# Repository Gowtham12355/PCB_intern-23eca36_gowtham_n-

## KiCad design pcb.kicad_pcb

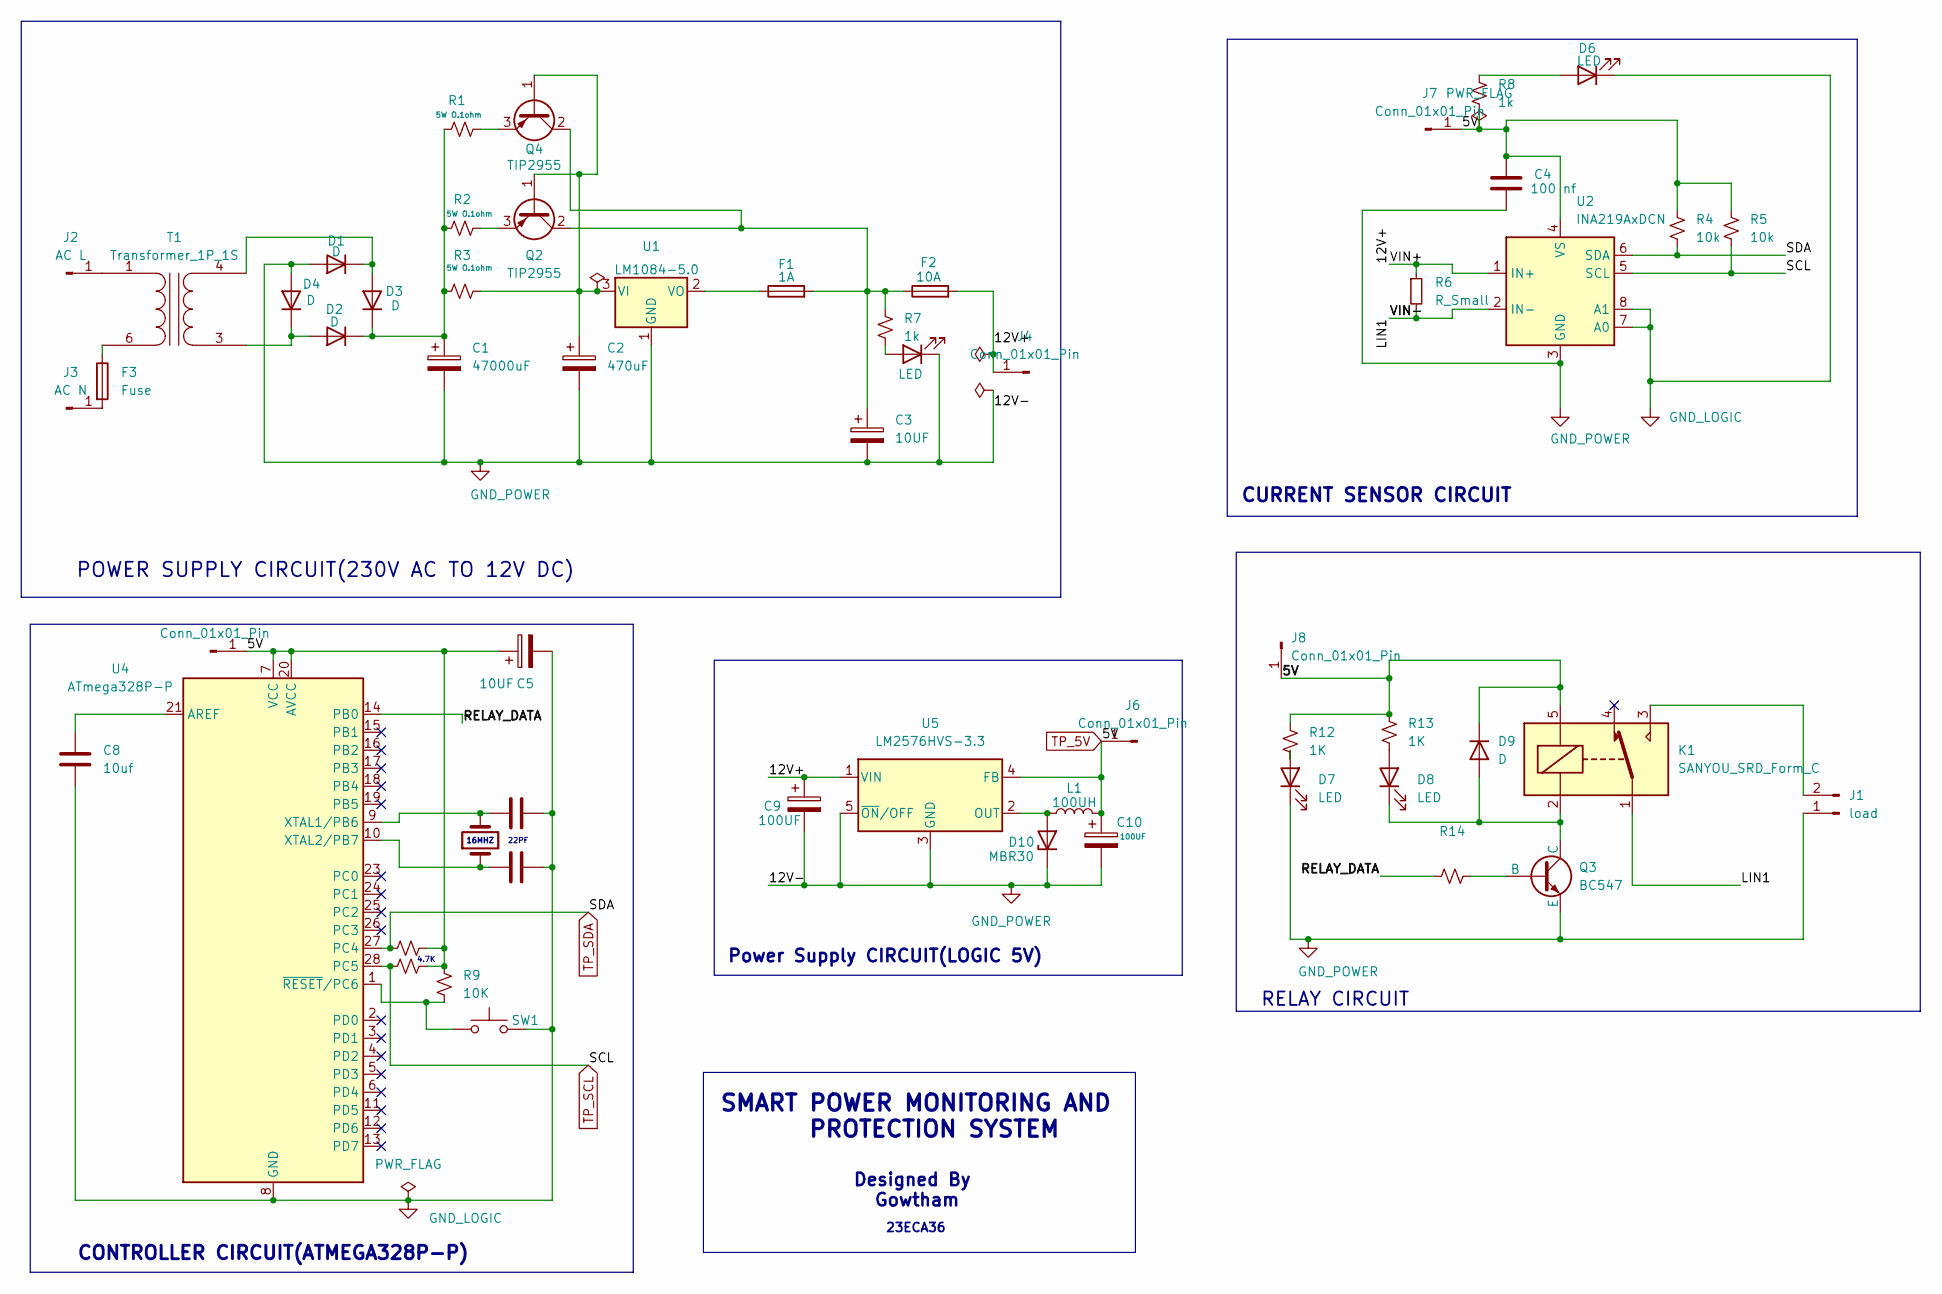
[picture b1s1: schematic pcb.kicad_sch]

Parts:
C1: 47000uF; CP_Radial_D18.0mm_P7.50mm
C2: 470uF; CP_Radial_D8.0mm_P5.00mm
C3: 10UF; CP_Radial_D8.0mm_P5.00mm
C4: 100 nf; C_0603_1608Metric
C5: 10UF; CP_Elec_6.3x5.7
C6, C7: C; C_0603_1608Metric_Pad1.08x0.95mm_HandSolder
C8: 10uf; C_0603_1608Metric_Pad1.08x0.95mm_HandSolder
C9, C10: 100UF; C_1210_3225Metric_Pad1.33x2.70mm_HandSolder
D1, D2, D3, D4: D; D_DO-201AE_P15.24mm_Horizontal
D5: LED; LED_D3.0mm
D6, D7, D8: LED; LED_1206_3216Metric_Pad1.42x1.75mm_HandSolder
D9: D; D_1206_3216Metric_Pad1.42x1.75mm_HandSolder
D10: MBR30; D_SOD-323
F1: 1A; Fuse_SunFuse-6HP
F2: 10A; Fuse_SunFuse-6HP
F3: Fuse; Fuse_SunFuse-6HP
J1: load; TerminalBlock_Phoenix_MKDS-1,5-2-5.08_1x02_P5.08mm_Horizont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
J2: AC L; Pin_D0.9mm_L10.0mm_W2.4mm_FlatFork
J3: AC N; Pin_D0.9mm_L10.0mm_W2.4mm_FlatFork
J4, J5, J6, J7, J8: Conn_01x01_Pin; TestPoint_Pad_D1.0mm
K1: SANYOU_SRD_Form_C; Relay_SPDT_SANYOU_SRD_Series_Form_C
L1: 100UH; L_Coilcraft_2929SQ-501
Q2, Q4: TIP2955; TO-218-3_Vertical
Q3: BC547; SC-59
R1, R2, R3: 5W O.1ohm; R_Axial_DIN0207_L6.3mm_D2.5mm_P5.08mm_Vertical
R4, R5: 10k; R_0603_1608Metric_Pad0.98x0.95mm_HandSolder
R6: R_Small; R_2010_5025Metric
R7: 1k; R_Axial_DIN0204_L3.6mm_D1.6mm_P2.54mm_Vertical
R8: 1k; R_0603_1608Metric
R9: 10K; R_0603_1608Metric_Pad0.98x0.95mm_HandSolder
R10, R11, R14: R_Small_US; R_0603_1608Metric_Pad0.98x0.95mm_HandSolder
R12, R13: 1K; R_0603_1608Metric_Pad0.98x0.95mm_HandSolder
SW1: SW_Push; SW_Push_1TS009xxxx-xxxx-xxxx_6x6x5mm
T1: Transformer_1P_1S; Transformer_Triad_VPP16-310
U1: LM1084-5.0; TO-218-3_Vertical
U2: INA219AxDCN; SOT-23-8
U4: ATmega328P-P; DIP-28_W7.62mm
U5: LM2576HVS-3.3; TO-263-5_TabPin3
Y1: Crystal; Crystal_AT310_D3.0mm_L10.0mm_Vertical

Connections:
/12V+: C9.1, F2.2, J4.1, R6.1, U2.1 (IN+), U5.1 (VIN)
/LIN1: K1.1, R6.2, U2.2 (IN-)
/RELAY_DATA: R14.1, U4.14 (PB0)
GND_LOGIC: C5.2, C6.2, C7.2, C8.2, D6.1 (K), SW1.2, U2.7 (A0), U2.8 (A1), U4.8 (GND), U4.22 (GND)
GND_POWER: C1.2, C2.2, C3.2, C4.2, C9.2, C10.2, D1.2 (A), D4.2 (A), D5.1 (K), D7.1 (K), D10.1 (K), J1.1, Q3.3 (E), U1.1 (GND), U2.3 (GND), U5.3 (GND), U5.5 (~ON/OFF)
unnamed: D1.1 (K), D3.2 (A), T1.4 (SB)
unnamed: D2.2 (A), D4.1 (K), T1.3 (SA)
unnamed: C1.1, D2.1 (K), D3.1 (K), R1.1, R2.1, R3.1
unnamed: D5.2 (A), R7.2
unnamed: D6.2 (A), R8.1
unnamed: D7.2 (A), R12.2
unnamed: D8.2 (A), R13.2
unnamed: D8.1 (K), D9.2 (A), K1.2, Q3.1 (C)
unnamed: D10.2 (A), L1.1, U5.2 (OUT)
unnamed: J1.2, K1.3
unnamed: J2.1, T1.1 (AA)
unnamed: F3.2, J3.1
unnamed: C2.1, Q2.1 (B), Q4.1 (B), R3.2, U1.3 (VI)
unnamed: C3.1, F1.2, F2.1, Q2.2 (C), Q4.2 (C), R7.1
unnamed: Q2.3 (E), R2.2
unnamed: Q3.2 (B), R14.2
unnamed: Q4.3 (E), R1.2
unnamed: F3.1, T1.6 (AB)
unnamed: F1.1, U1.2 (VO)
unnamed: C8.1, U4.21 (AREF)
unnamed: C6.1, U4.9 (XTAL1/PB6), Y1.2
unnamed: C7.1, U4.10 (XTAL2/PB7), Y1.1
unnamed: R9.2, SW1.1, U4.1 (~RESET/PC6)
TP_5V: C4.1, C5.1, C10.1, D9.1 (K), J5.1, J6.1, J7.1, J8.1, K1.5, L1.2, R4.1, R5.1, R8.2, R9.1, R10.2, R11.2, R12.1, R13.1, U2.4 (VS), U4.7 (VCC), U4.20 (AVCC), U5.4 (FB)
TP_SCL: R5.2, R10.1, U2.5 (SCL), U4.28 (PC5)
TP_SDA: R4.2, R11.1, U2.6 (SDA), U4.27 (PC4)

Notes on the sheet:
Power Supply CIRCUIT(LOGIC 5V)
SMART POWER MONITORING AND PROTECTION SYSTEM
Designed By Gowtham
4.7K
CURRENT SENSOR CIRCUIT
CONTROLLER CIRCUIT(ATMEGA328P-P)
POWER SUPPLY CIRCUIT(230V AC TO 12V DC)
16MHZ
RELAY CIRCUIT
23ECA36
22PF

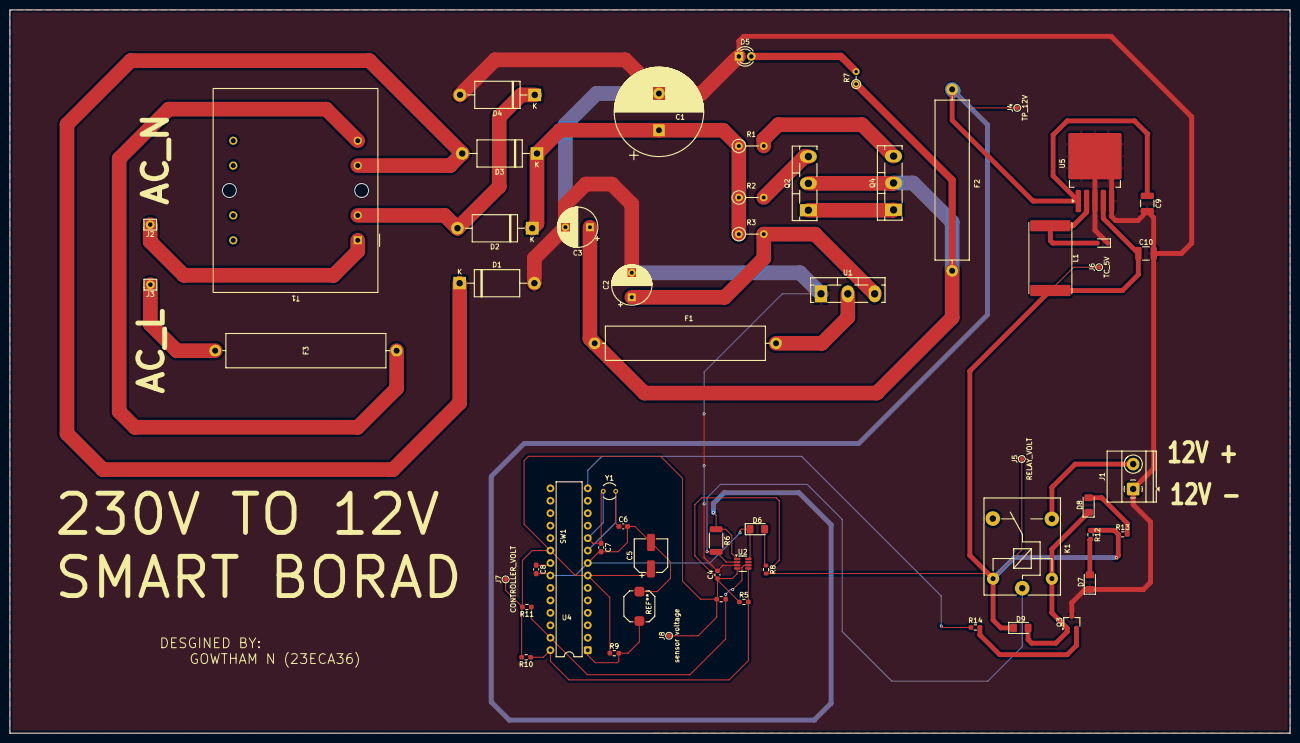
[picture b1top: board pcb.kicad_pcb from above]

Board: 2 copper layers, 261.1 x 147.5 mm, 57 parts (0 on the bottom side), 31 nets.

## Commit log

2026-02-12 Add initial content to gowtham file
